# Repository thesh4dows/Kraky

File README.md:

# Kraky

Kraky is a DIY open-hardware project inspired by the Flipper Zero. It uses affordable parts and focuses on an educational, modular, and easy to repair aspect.

I started this journey with just a sketchbook and a lot of passion. The first thing i did was look up all the components and make a list, so i would have a clear path for the next steps.
Then i've done the elettric schematic, once i redacted all the components i started with the elettric schematic and connecting all the components to outline the scheme for the PCB.
Once i've connected all the components i've moved on making the PCB, making the PCB was easy because all the connections where there the only problem was not get tangled in that mess but i've succeded.
With all the elettronics sorted out i moved on with the CAD and firmware, and even if they are a bit rought i'm looking forward to improving them.

For the assemble I suggest putting first the TP4056 and the U.FL connector, because they are smd soldered, and then I suggest putting the RFM98W-433S2, because is the module with the smallest pins, and the you can decide freely the order of the soldering from now on, you can also decide to use some header pins so you can use the modules in other projects.

---

## Main Components

| Function | Component |
|--------|----------|
| Logic board / Wi-Fi / Bluetooth | **ESP32-S3** |
| Sub-GHz | **RFM98W-433S2** |
| RFID | **RDM6300** |
| NFC | **PN532** |
| Battery charger | **TP4056** |
| Battery | **1000 mAh Li-ion** |
| IR Receiver | **TSOP38238** |
| IR Transmitter | **IR LED** |
| Speaker | **Passive** |
| GPIO Expansion | **10 Female GPIO pins** |
| microSD Slot | **CM1624** *(not yet implemented in PCB)* |
| Buttons | **4 tactile buttons** |
| Oscilloscope | **MPU6050** |
| Display | **Oled Display** |

---

## Future Features 

- microSD support
- new pcb more small
- modularity

---

## WIRING DIAGRAM

---

## PCB 

---

## PCB AND 3D RENDER COMBINED

---

## BOM LIST
| Component | Link |
|--------|----------|
| **ESP32-S3** | [Aliexpress](https://it.aliexpress.com/item/1005009962649997.html?spm=a2g0o.cart.0.0.5d8818fcuRNXq9&mp=1&pdp_npi=6%40dis%21EUR%21EUR%208.05%21EUR%207.33%21%21EUR%207.33%21%21%21%4021038e1e17694574608762210ead3b%2112000050714164641%21ct%21IT%214906144315%21%211%210%21&gatewayAdapt=glo2ita) |
| **RFM98W-433S2** | [Aliexpress](https://it.aliexpress.com/item/1005008889705168.html?spm=a2g0o.cart.0.0.5d8818fcuRNXq9&mp=1&pdp_npi=6%40dis%21EUR%21EUR%2013.69%21EUR%2013.69%21%21EUR%2013.69%21%21%21%4021038e1e17694574632892284ead3b%2112000047093365845%21ct%21IT%214906144315%21%211%210%21&gatewayAdapt=glo2ita) |
| **RDM6300** | [Aliexpress](https://it.aliexpress.com/item/32878097013.html?spm=a2g0o.cart.0.0.5d8818fcuRNXq9&mp=1&pdp_npi=6%40dis%21EUR%21EUR%203.16%21EUR%203.16%21%21EUR%203.16%21%21%21%4021038e1e17694574632892284ead3b%2165586589948%21ct%21IT%214906144315%21%211%210%21&gatewayAdapt=glo2ita) |
| **PN532** | [Aliexpress](https://it.aliexpress.com/item/1005008554785133.html?spm=a2g0o.cart.0.0.5d8818fcuRNXq9&mp=1&pdp_npi=6%40dis%21EUR%21EUR%206.69%21EUR%203.07%21%21EUR%203.01%21%21%21%4021038e1e17694574608762210ead3b%2112000045690199375%21ct%21IT%214906144315%21%211%210%21&gatewayAdapt=glo2ita) |
| **TP4056** | [Aliexpress](https://it.aliexpress.com/item/1005006520142503.html?spm=a2g0o.productlist.main.9.370dQqVLQqVLdw&algo_pvid=b4bbd4a5-a930-4122-b394-fd39a9f770f2&algo_exp_id=b4bbd4a5-a930-4122-b394-fd39a9f770f2-8&pdp_ext_f=%7B%22order%22%3A%2220%22%2C%22spu_best_type%22%3A%22price%22%2C%22eval%22%3A%221%22%2C%22fromPage%22%3A%22search%22%7D&pdp_npi=6%40dis%21EUR%219.23%214.34%21%21%2174.32%2134.93%21%402103834817694577274995958e83e4%2112000037514108642%21sea%21IT%214906144315%21X%211%210%21n_tag%3A-29919%3Bd%3Af5869dfc%3Bm03_new_user%3A-29895&curPageLogUid=HOVHMltfnK6x&utparam-url=scene%3Asearch%7Cquery_from%3A%7Cx_object_id%3A1005006520142503%7C_p_origin_prod%3A) |
| **Battery** | [Aliexpress](https://it.aliexpress.com/item/1005006284232365.html?spm=a2g0o.cart.0.0.1eb718fcbElXUV&mp=1&pdp_npi=6%40dis%21EUR%21EUR%2017.40%21EUR%2010.09%21%21EUR%209.59%21%21%21%4021038e1e17694577674865712ead3b%2112000036605860873%21ct%21IT%214906144315%21%211%210%21&gatewayAdapt=glo2ita) |
| **TSOP38238** | [Aliexpress](https://it.aliexpress.com/item/32949322622.html?spm=a2g0o.cart.0.0.1eb718fcbElXUV&mp=1&pdp_npi=6%40dis%21EUR%21EUR%202.24%21EUR%202.24%21%21EUR%202.24%21%21%21%4021038e1e17694577674865712ead3b%2166318108356%21ct%21IT%214906144315%21%211%210%21&gatewayAdapt=glo2ita) |
| IR LED | [Aliexpress](https://it.aliexpress.com/item/1005006286672244.html?spm=a2g0o.detail.0.0.5c75OQANOQANd8&mp=1&pdp_npi=6%40dis%21EUR%21EUR%201.24%21EUR%201.24%21%21EUR%201.24%21%21%21%40211b431017709169710087494e4c02%2112000036615490369%21ct%21IT%214906144315%21%211%210%21&pdp_ext_f=%7B%22cart2PdpParams%22%3A%7B%22pdpBusinessMode%22%3A%22retail%22%7D%7D&_gl=1*5a8ami*_gcl_aw*R0NMLjE3NzAyMTg4NDcuQ2owS0NRaUEtWXZNQmhEdEFSSXNBSFp1VXpJOWRqODVuQVpGTGNfQ01JM29Qc2NQNFczWDk2NVR4YWJFX1FHRkNUZU5fZFY5YWdlb3RvMGFBamw1RUFMd193Y0I.*_gcl_dc*R0NMLjE3NzAyMTg4NDcuQ2owS0NRaUEtWXZNQmhEdEFSSXNBSFp1VXpJOWRqODVuQVpGTGNfQ01JM29Qc2NQNFczWDk2NVR4YWJFX1FHRkNUZU5fZFY5YWdlb3RvMGFBamw1RUFMd193Y0I.*_gcl_au*MTk0Mzg4NTc4MC4xNzYzNzM5NDY4*_ga*MTEzNzE4MTYwMTA1MjIyMS4xNzI2NTAwNTQ2NTA5*_ga_VED1YSGNC7*czE3NzA5MTU1ODUkbzI1JGcxJHQxNzcwOTE3MDExJGoxNCRsMCRoMA..&gatewayAdapt=glo2ita) |
| Speaker | [Aliexpress](https://it.aliexpress.com/item/1005008743722885.html?spm=a2g0o.cart.0.0.1eb718fcbElXUV&mp=1&pdp_npi=6%40dis%21EUR%21EUR%204.31%21EUR%202.07%21%21EUR%202.05%21%21%21%4021038e1e17694577658065675ead3b%2112000046486255672%21ct%21IT%214906144315%21%211%210%21&gatewayAdapt=glo2ita) |
| 10 Female GPIO pins | [Aliexpress](https://it.aliexpress.com/item/1005008966856219.html?spm=a2g0o.productlist.main.7.400c469fw7ynlD&algo_pvid=9f47b1bf-4ccb-44b8-978c-11ec9fc6ee57&algo_exp_id=9f47b1bf-4ccb-44b8-978c-11ec9fc6ee57-6&pdp_ext_f=%7B%22order%22%3A%22554%22%2C%22eval%22%3A%221%22%2C%22fromPage%22%3A%22search%22%7D&pdp_npi=6%40dis%21EUR%211.36%211.21%21%21%211.57%211.40%21%4021038e1e17694578315316029ead41%2112000047493524680%21sea%21IT%214906144315%21X%211%210%21n_tag%3A-29919%3Bd%3Af5869dfc%3Bm03_new_user%3A-29895%3BpisId%3A5000000198855826&curPageLogUid=SOrvoxlj0a91&utparam-url=scene%3Asearch%7Cquery_from%3A%7Cx_object_id%3A1005008966856219%7C_p_origin_prod%3A) |
| **10pF** | [Aliexpress](https://it.aliexpress.com/item/4001146250895.html?spm=a2g0o.productlist.main.12.6001XDEgXDEgfW&aem_p4p_detail=202602120809274082320741397240005427668&algo_pvid=a04d9bc2-151b-457c-b0a5-42ba286d77e0&algo_exp_id=a04d9bc2-151b-457c-b0a5-42ba286d77e0-11&pdp_ext_f=%7B%22order%22%3A%2288%22%2C%22eval%22%3A%221%22%2C%22fromPage%22%3A%22search%22%7D&pdp_npi=6%40dis%21EUR%211.52%211.47%21%21%211.76%211.70%21%402103963717709125677277103e20f4%2110000014890782446%21sea%21IT%214906144315%21X%211%210%21n_tag%3A-29919%3Bd%3Af5869dfc%3Bm03_new_user%3A-29895&curPageLogUid=z2f4APj81CW1&utparam-url=scene%3Asearch%7Cquery_from%3A%7Cx_object_id%3A4001146250895%7C_p_origin_prod%3A&search_p4p_id=202602120809274082320741397240005427668_3) |
| Buttons | [Aliexpress](https://it.aliexpress.com/item/1005003751942617.html?spm=a2g0o.productlist.main.6.7b66UgMCUgMC2v&algo_pvid=90b119e5-116b-44ca-8d19-1b1e01badc9a&algo_exp_id=90b119e5-116b-44ca-8d19-1b1e01badc9a-5&pdp_ext_f=%7B%22order%22%3A%22457%22%2C%22eval%22%3A%221%22%2C%22fromPage%22%3A%22search%22%7D&pdp_npi=6%40dis%21EUR%212.68%212.32%21%21%2121.57%2118.69%21%40211b618e17694579682652136e0d37%2112000027951043689%21sea%21IT%214906144315%21X%211%210%21n_tag%3A-29919%3Bd%3Af5869dfc%3Bm03_new_user%3A-29895%3BpisId%3A5000000198855826&curPageLogUid=h3YPZfgd06kE&utparam-url=scene%3Asearch%7Cquery_from%3A%7Cx_object_id%3A1005003751942617%7C_p_origin_prod%3A) |
| MPU6050 | [Aliexpress](https://it.aliexpress.com/item/1005010057794277.html?spm=a2g0o.cart.0.0.1eb718fcbElXUV&mp=1&pdp_npi=6%40dis%21EUR%21EUR%201.89%21EUR%201.89%21%21EUR%201.89%21%21%21%4021038e1e17694577658065675ead3b%2112000050979433010%21ct%21IT%214906144315%21%211%210%21&gatewayAdapt=glo2ita) |
| **100nF** | [Aliexpress](https://it.aliexpress.com/item/1005005691676032.html?spm=a2g0o.cart.0.0.1eb718fcbElXUV&mp=1&pdp_npi=6%40dis%21EUR%21EUR%202.24%21EUR%201.31%21%21EUR%201.31%21%21%21%4021038e1e17694577658065675ead3b%2112000034022594969%21ct%21IT%214906144315%21%211%210%21&gatewayAdapt=glo2ita) |
| **Battery connector** | [Aliexpress](https://it.aliexpress.com/item/1005009883885132.html?spm=a2g0o.cart.0.0.1eb718fcbElXUV&mp=1&pdp_npi=6%40dis%21EUR%21EUR%204.30%21EUR%201.92%21%21EUR%201.92%21%21%21%4021038e1e17694577658065675ead3b%2112000050645799497%21ct%21IT%214906144315%21%213%210%21&gatewayAdapt=glo2ita) |
| **2N3904** | [Aliexpress](https://it.aliexpress.com/item/1005009725419981.html?spm=a2g0o.cart.0.0.1eb718fcbElXUV&mp=1&pdp_npi=6%40dis%21EUR%21EUR%204.02%21EUR%201.89%21%21EUR%201.87%21%21%21%4021038e1e17694577658065675ead3b%2112000049959909602%21ct%21IT%214906144315%21%211%210%21&gatewayAdapt=glo2ita) |
| **BLM21PG331SN1D** | [Aliexpress](https://it.aliexpress.com/item/1005011660929872.html?spm=a2g0o.cart.0.0.447618fc6TVgoa&mp=1&pdp_npi=6%40dis%21EUR%21EUR%200.46%21EUR%200.45%21%21EUR%200.44%21%21%21%40211b431017709170583751647e4c02%2112000056178400547%21ct%21IT%214906144315%21%211%210%21&gatewayAdapt=glo2ita) | 
| **Antenna** | [Aliexpress](https://www.aliexpress.com/item/1005007502415094.html?spm=a2g0o.cart.0.0.235318fc7Us4Rx&mp=1&pdp_npi=6%40dis%21EUR%21EUR%201.47%21EUR%201.47%21%21EUR%201.47%21%21%21%40211b80f717697046718262403e31b3%2112000041044934823%21ct%21IT%214906144315%21%212%210%21) |
| **1K ohm** | [Aliexpress](https://it.aliexpress.com/item/1005008049421850.html?spm=a2g0o.productlist.main.5.339e2072xf4Fp6&algo_pvid=60a0f9d2-cb3a-4061-b250-3a89b5594825&algo_exp_id=60a0f9d2-cb3a-4061-b250-3a89b5594825-4&pdp_ext_f=%7B%22order%22%3A%221081%22%2C%22eval%22%3A%221%22%2C%22fromPage%22%3A%22search%22%7D&pdp_npi=6%40dis%21EUR%212.03%211.29%21%21%2116.36%2110.40%21%40211b61bb17694589696196228e2a30%2112000043433742591%21sea%21IT%214906144315%21X%211%210%21n_tag%3A-29919%3Bd%3Af5869dfc%3Bm03_new_user%3A-29895%3BpisId%3A5000000198855826&curPageLogUid=0AoDAOfCkDU4&utparam-url=scene%3Asearch%7Cquery_from%3A%7Cx_object_id%3A1005008049421850%7C_p_origin_prod%3A) |
| **10K ohm** | [Aliexpress](https://it.aliexpress.com/item/1005008049421850.html?spm=a2g0o.productlist.main.5.339e2072xf4Fp6&algo_pvid=60a0f9d2-cb3a-4061-b250-3a89b5594825&algo_exp_id=60a0f9d2-cb3a-4061-b250-3a89b5594825-4&pdp_ext_f=%7B%22order%22%3A%221081%22%2C%22eval%22%3A%221%22%2C%22fromPage%22%3A%22search%22%7D&pdp_npi=6%40dis%21EUR%212.03%211.29%21%21%2116.36%2110.40%21%40211b61bb17694589696196228e2a30%2112000043433742591%21sea%21IT%214906144315%21X%211%210%21n_tag%3A-29919%3Bd%3Af5869dfc%3Bm03_new_user%3A-29895%3BpisId%3A5000000198855826&curPageLogUid=0AoDAOfCkDU4&utparam-url=scene%3Asearch%7Cquery_from%3A%7Cx_object_id%3A1005008049421850%7C_p_origin_prod%3A) |
| **100 ohm** | [Aliexpress](https://it.aliexpress.com/item/1005008049421850.html?spm=a2g0o.productlist.main.5.339e2072xf4Fp6&algo_pvid=60a0f9d2-cb3a-4061-b250-3a89b5594825&algo_exp_id=60a0f9d2-cb3a-4061-b250-3a89b5594825-4&pdp_ext_f=%7B%22order%22%3A%221081%22%2C%22eval%22%3A%221%22%2C%22fromPage%22%3A%22search%22%7D&pdp_npi=6%40dis%21EUR%212.03%211.29%21%21%2116.36%2110.40%21%40211b61bb17694589696196228e2a30%2112000043433742591%21sea%21IT%214906144315%21X%211%210%21n_tag%3A-29919%3Bd%3Af5869dfc%3Bm03_new_user%3A-29895%3BpisId%3A5000000198855826&curPageLogUid=0AoDAOfCkDU4&utparam-url=scene%3Asearch%7Cquery_from%3A%7Cx_object_id%3A1005008049421850%7C_p_origin_prod%3A) |
| **Oled Display** | [Aliexpress](https://it.aliexpress.com/item/1005009180825215.html?spm=a2g0o.productlist.main.2.3d2d471bqR6akO&algo_pvid=3bf73457-57de-4609-b5e8-c52edf535fa0&algo_exp_id=3bf73457-57de-4609-b5e8-c52edf535fa0-1&pdp_ext_f=%7B%22order%22%3A%2279%22%2C%22eval%22%3A%221%22%2C%22fromPage%22%3A%22search%22%7D&pdp_npi=6%40dis%21EUR%213.36%213.06%21%21%213.90%213.55%21%402103890917695190995271643e41ef%2112000048217113638%21sea%21IT%214906144315%21X%211%210%21n_tag%3A-29919%3Bd%3Af5869dfc%3Bm03_new_user%3A-29895%3BpisId%3A5000000198855826&curPageLogUid=jkERcBiiep5C&utparam-url=scene%3Asearch%7Cquery_from%3A%7Cx_object_id%3A1005009180825215%7C_p_origin_prod%3A) |
| **Led** | [Aliexpress](https://it.aliexpress.com/item/1005006463058075.html?spm=a2g0o.productlist.main.5.705af8d9MykV40&algo_pvid=cd9d209a-c5d1-4345-918b-1aef88c26f78&algo_exp_id=cd9d209a-c5d1-4345-918b-1aef88c26f78-4&pdp_ext_f=%7B%22order%22%3A%221437%22%2C%22spu_best_type%22%3A%22price%22%2C%22eval%22%3A%221%22%2C%22fromPage%22%3A%22search%22%7D&pdp_npi=6%40dis%21EUR%211.66%211.17%21%21%2113.42%219.48%21%402103834817695464502855059e28c6%2112000037284712619%21sea%21IT%210%21ABX%211%210%21n_tag%3A-29910%3Bd%3Af5869dfc%3Bm03_new_user%3A-29895%3BpisId%3A5000000197840834&curPageLogUid=CU7YloDPjo8Z&utparam-url=scene%3Asearch%7Cquery_from%3A%7Cx_object_id%3A1005006463058075%7C_p_origin_prod%3A) |
| **Step Up** | [Aliexpress](https://it.aliexpress.com/item/1005010399811030.html?spm=a2g0o.detail.0.0.5c75OQANOQANd8&mp=1&pdp_npi=6%40dis%21EUR%21EUR%205.30%21EUR%202.54%21%21EUR%202.52%21%21%21%40211b431017709169710087494e4c02%2112000052282921768%21ct%21IT%214906144315%21%211%210%21&_gl=1*nbieyi*_gcl_aw*R0NMLjE3NzAyMTg4NDcuQ2owS0NRaUEtWXZNQmhEdEFSSXNBSFp1VXpJOWRqODVuQVpGTGNfQ01JM29Qc2NQNFczWDk2NVR4YWJFX1FHRkNUZU5fZFY5YWdlb3RvMGFBamw1RUFMd193Y0I.*_gcl_dc*R0NMLjE3NzAyMTg4NDcuQ2owS0NRaUEtWXZNQmhEdEFSSXNBSFp1VXpJOWRqODVuQVpGTGNfQ01JM29Qc2NQNFczWDk2NVR4YWJFX1FHRkNUZU5fZFY5YWdlb3RvMGFBamw1RUFMd193Y0I.*_gcl_au*MTk0Mzg4NTc4MC4xNzYzNzM5NDY4*_ga*MTEzNzE4MTYwMTA1MjIyMS4xNzI2NTAwNTQ2NTA5*_ga_VED1YSGNC7*czE3NzA5MTU1ODUkbzI1JGcxJHQxNzcwOTE2OTcwJGo1NSRsMCRoMA..&gatewayAdapt=glo2ita) |
| **Switch** | [Aliexpress](https://it.aliexpress.com/item/1005004402594340.html?spm=a2g0o.productlist.main.8.6821RzZiRzZivU&aem_p4p_detail=20260128050330766496466031320001147087&algo_pvid=5d157c24-975d-4016-b80c-94e148440976&algo_exp_id=5d157c24-975d-4016-b80c-94e148440976-7&pdp_ext_f=%7B%22order%22%3A%22724%22%2C%22spu_best_type%22%3A%22service%22%2C%22eval%22%3A%221%22%2C%22fromPage%22%3A%22search%22%7D&pdp_npi=6%40dis%21EUR%212.14%211.87%21%21%212.51%212.20%21%40211b813b17696054100286413e9a8e%2112000029051761216%21sea%21IT%214906144315%21X%211%210%21n_tag%3A-29919%3Bd%3Af5869dfc%3Bm03_new_user%3A-29895%3BpisId%3A5000000198855826&curPageLogUid=7JLAO8Dg6auy&utparam-url=scene%3Asearch%7Cquery_from%3A%7Cx_object_id%3A1005004402594340%7C_p_origin_prod%3A&search_p4p_id=20260128050330766496466031320001147087_2) |
| **U.FL connector** | [Aliexpress](https://www.aliexpress.com/item/4001125536245.html?spm=a2g0o.cart.0.0.235318fc7Us4Rx&mp=1&pdp_npi=6%40dis%21EUR%21EUR%201.94%21EUR%201.90%21%21EUR%201.90%21%21%21%40211b80f717697046718262403e31b3%2110000014628446564%21ct%21IT%214906144315%21%211%210%21) |

---

## Responsible Use

Kraky is built to make it easier for anyone to explore and understand how multifunction electronic devices work in everyday life.
It’s not intended for bypassing security systems or breaking any laws.

All features are implemented with an educational and experimental focus.

---

## Tools Used

- KiCad 9
- Fusion360
- PlatformIO

---

## Project Status

This project is **work in progress (WIP)**.  
Future updates will include:

- microSD implementation
- firmware development
- smaller PCB and SMD soldered components 

---

## Contributing

Kraky is an **open and educational project**.  
Feedback, suggestions, and improvements are always welcome.

---

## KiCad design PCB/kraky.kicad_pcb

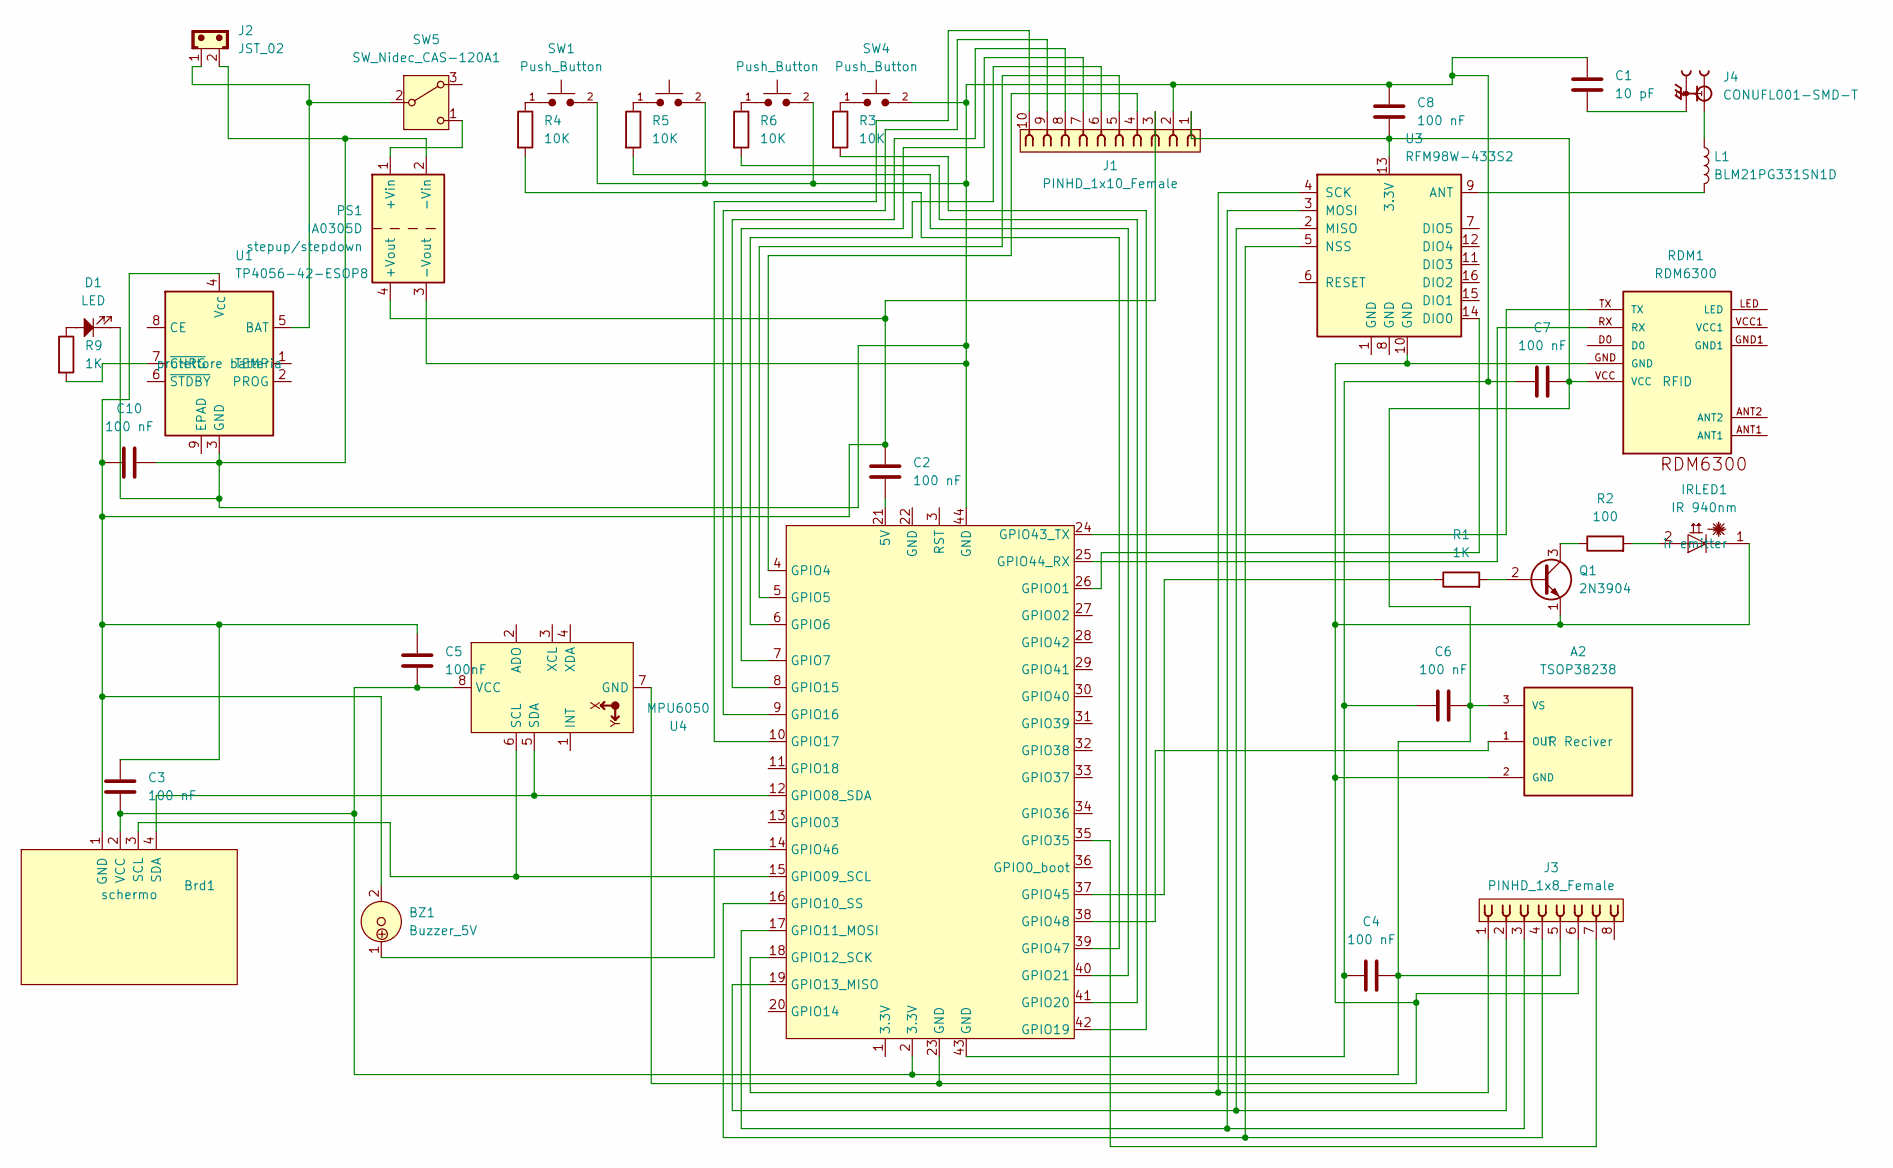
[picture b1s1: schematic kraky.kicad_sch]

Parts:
A2: TSOP38238; XDCR_TSOP38238; PARTREV 1.7
BZ1: Buzzer_5V; MagneticBuzzer_ProSignal_ABT-410-RC
Brd1: SSD1306; 128x64OLED
C1: 10 pF; C_Axial_L3.8mm_D2.6mm_P7.50mm_Horizontal
C2, C3, C4, C6, C7, C8, C10: 100 nF; C_Axial_L3.8mm_D2.6mm_P7.50mm_Horizontal
C5: 100nF; C_Axial_L3.8mm_D2.6mm_P7.50mm_Horizontal
D1: LED; LED_D5.0mm
IRLED1: IR 940nm; LED_D5.0mm
J1: PINHD_1x10_Female; PinSocket_1x10_P2.54mm_Vertical
J2: JST_02; JST_EH_B2B-EH-A_1x02_P2.50mm_Vertical
J3: PINHD_1x8_Female; PinSocket_1x08_P2.54mm_Vertical
J4: CONUFL001-SMD-T; LINX_CONUFL001-SMD-T
L1: BLM21PG331SN1D; R_0805_2012Metric
PS1: IA0305D; step up kraky
Q1: 2N3904; TO-92_Inline
R1, R9: 1K; R_Axial_DIN0204_L3.6mm_D1.6mm_P5.08mm_Horizontal
R2: 100; R_Axial_DIN0204_L3.6mm_D1.6mm_P5.08mm_Horizontal
R3, R4, R5, R6: 10K; R_Axial_DIN0204_L3.6mm_D1.6mm_P5.08mm_Horizontal
RDM1: RDM6300
SW1, SW2, SW3, SW4: Push_Button; SW_PUSH_6mm
SW5: SW_Nidec_CAS-120A1; SW_Slide_SPDT_Angled_CK_OS102011MA1Q
U1: TP4056-42-ESOP8; SOIC-8-1EP_3.9x4.9mm_P1.27mm_EP2.41x3.3mm_ThermalVias
U2: esp32-s3
U3: RFM98W-433S2; HOPERF_RFM9XW_THT
U4: MPU6050; MPU6050_Breakout

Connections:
unnamed: A2.2 (GND), IRLED1.1 (C), J3.6, Q1.1 (E), RDM1.GND, U2.23 (GND), U3.10 (GND), U4.7 (GND)
unnamed: A2.1 (OUT), U2.38 (GPIO48)
unnamed: A2.3 (VS), Brd1.2 (VCC), C3.2, C4.1, C5.2, C6.1, C7.1, C8.2, J1.1, J3.5, RDM1.VCC, U2.2 (3.3V), U3.13 (3.3V), U4.8 (VCC)
unnamed: BZ1.2, Brd1.1 (GND), C2.1, C3.1, C5.1, C10.1, J1.3, PS1.4 (+Vout), U1.4 (V_{CC})
unnamed: Brd1.3 (SCL), U2.15 (GPIO09_SCL), U4.6 (SCL)
unnamed: Brd1.4 (SDA), U2.12 (GPIO08_SDA), U4.5 (SDA)
unnamed: C1.2, J4.2, J4.3
unnamed: D1.2, R9.1
unnamed: IRLED1.2 (A), R2.2
unnamed: J4.1, L1.1
unnamed: PS1.1 (+Vin), SW5.1 (C)
unnamed: C1.1, C4.2, C6.2, C7.2, C8.1, C10.2, D1.1, J1.2, J2.2, PS1.2 (-Vin), PS1.3 (-Vout), SW1.2, SW2.2, SW3.2, SW4.2, U1.3 (GND), U2.43 (GND), U2.44 (GND)
unnamed: Q1.2 (B), R1.2
unnamed: Q1.3 (C), R2.1
unnamed: R3.1, SW4.1
unnamed: R4.1, SW1.1
unnamed: R5.1, SW2.1
unnamed: R6.1, SW3.1
unnamed: J2.1, SW5.2 (B), U1.5 (BAT)
unnamed: R9.2, U1.7 (~CHRG)
unnamed: C2.2, U2.21 (5V)
unnamed: U2.26 (GPIO01), U3.14 (DIO0)
unnamed: J1.4, U2.4 (GPIO4)
unnamed: J1.5, U2.5 (GPIO5)
unnamed: J1.6, U2.6 (GPIO6)
unnamed: J1.7, U2.7 (GPIO7)
unnamed: J3.4, U2.16 (GPIO10_SS), U3.5 (NSS)
unnamed: J3.3, U2.17 (GPIO11_MOSI), U3.3 (MOSI)
unnamed: J3.1, U2.18 (GPIO12_SCK), U3.4 (SCK)
unnamed: J3.2, U2.19 (GPIO13_MISO), U3.2 (MISO)
unnamed: J1.8, U2.8 (GPIO15)
unnamed: J1.9, U2.9 (GPIO16)
unnamed: J1.10, U2.10 (GPIO17)
unnamed: R3.2, U2.42 (GPIO19)
unnamed: R6.2, U2.41 (GPIO20)
unnamed: R5.2, U2.40 (GPIO21)
unnamed: J3.7, U2.35 (GPIO35)
unnamed: RDM1.TX, U2.24 (GPIO43_TX)
unnamed: RDM1.RX, U2.25 (GPIO44_RX)
unnamed: R1.1, U2.37 (GPIO45)
unnamed: BZ1.1, U2.14 (GPIO46)
unnamed: R4.2, U2.39 (GPIO47)
unnamed: L1.2, U3.9 (ANT)

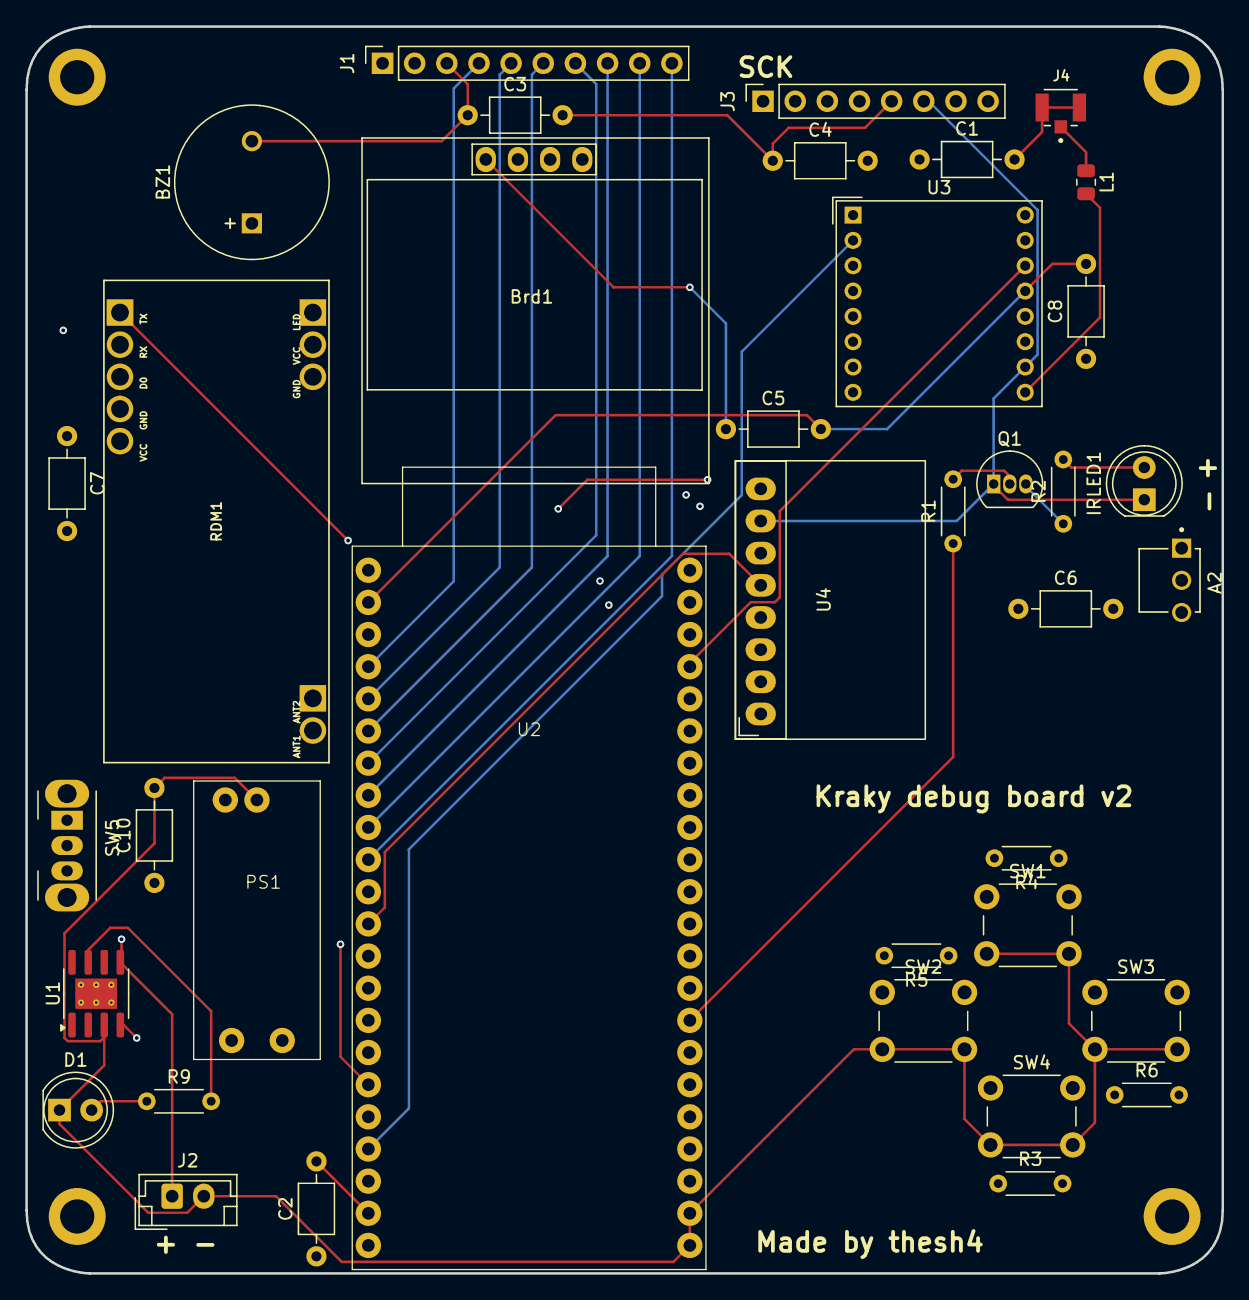
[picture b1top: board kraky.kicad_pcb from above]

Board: 4 copper layers, 94.5 x 98.5 mm, 42 parts (0 on the bottom side), 43 nets.

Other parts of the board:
buco1, buco2, buco3, buco4: MountingHole_2.7mm_M2.5_ISO14580_Pad

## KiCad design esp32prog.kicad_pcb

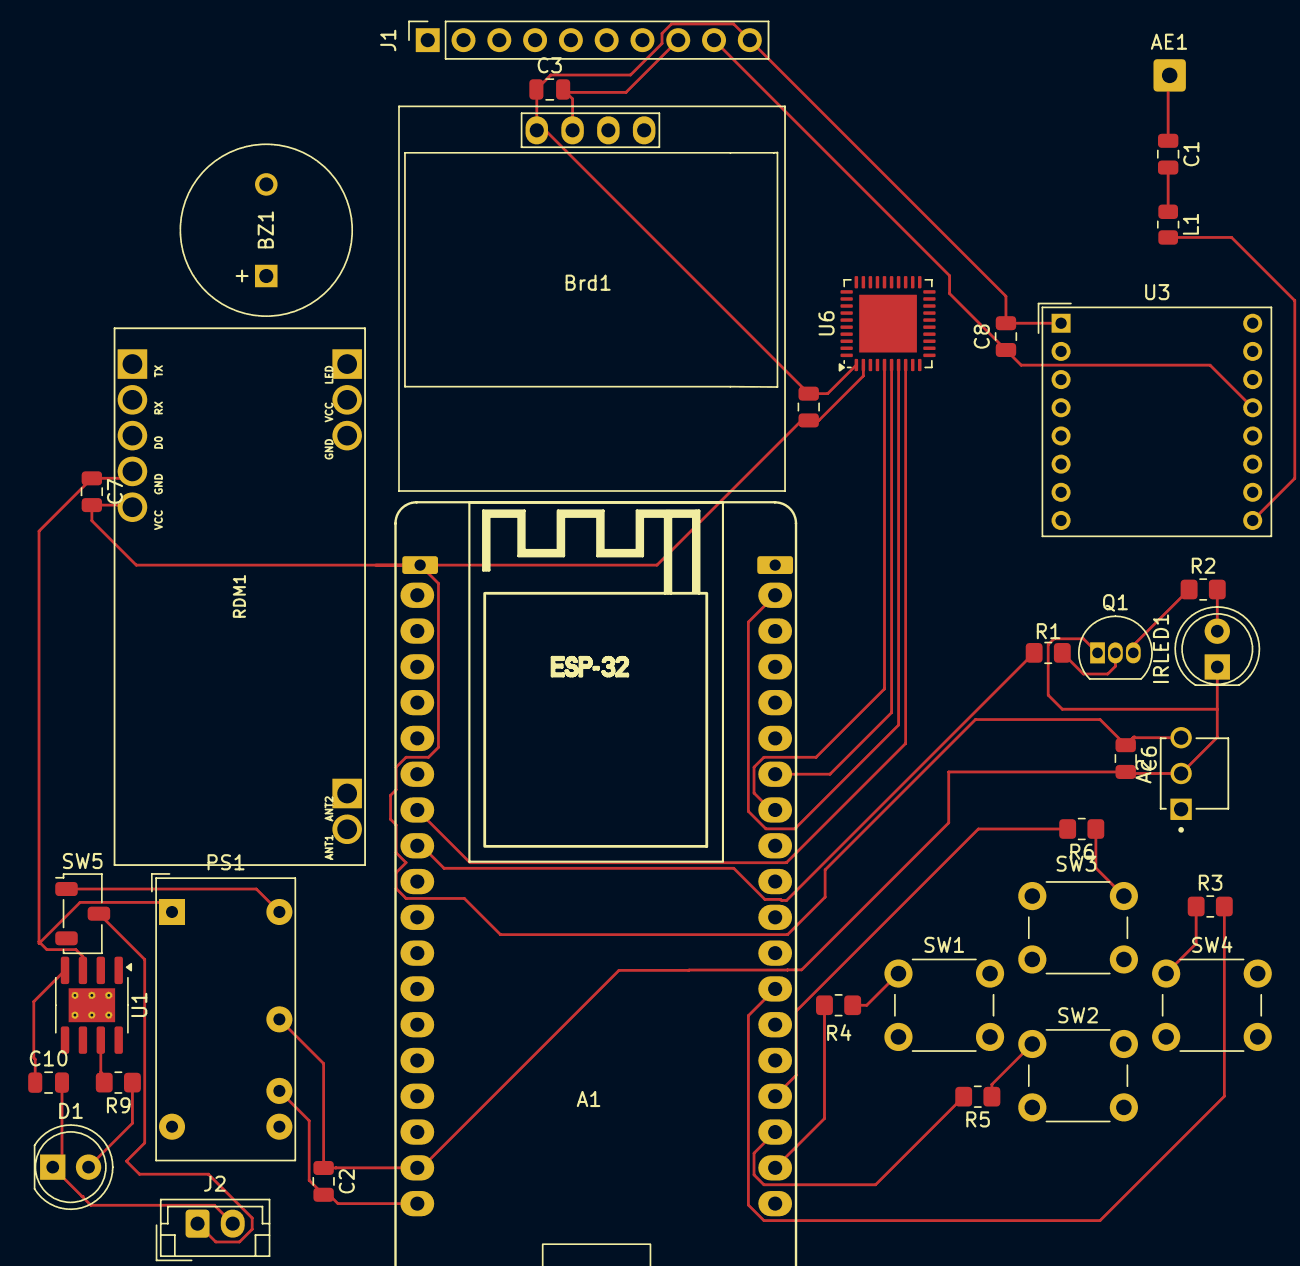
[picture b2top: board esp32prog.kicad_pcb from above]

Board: 4 copper layers, 36 parts (0 on the bottom side), 43 nets.

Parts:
A1: ESP32_DevKit_V1_DOIT_36GPIOs; DOIT_ESP32_DEVKIT_36Pins
A2: TSOP38238; XDCR_TSOP38238
AE1: Antenna; SolderWire-0.5sqmm_1x01_D0.9mm_OD2.3mm
BZ1: Buzzer_5V; MagneticBuzzer_ProSignal_ABT-410-RC
Brd1: SSD1306; 128x64OLED
C1: 10 pF; C_0805_2012Metric
C2, C3, C4, C6, C7, C8, C10: 100 nF; C_0805_2012Metric
D1: LED; LED_D5.0mm
IRLED1: IR 940nm; LED_D5.0mm
J1: PINHD_1x10_Female; PinSocket_1x10_P2.54mm_Vertical
J2: JST_02; JST_EH_B2B-EH-A_1x02_P2.50mm_Vertical
L1: BLM21PG331SN1D; R_0805_2012Metric
PS1: IA0305D; Converter_DCDC_XP_POWER-IAxxxxD_THT
Q1: 2N3904; TO-92_Inline
R1, R9: 1K; R_0805_2012Metric_Pad1.20x1.40mm_HandSolder
R2: 100; R_0805_2012Metric_Pad1.20x1.40mm_HandSolder
R3, R4, R5, R6: 10K; R_0805_2012Metric_Pad1.20x1.40mm_HandSolder
RDM1: RDM6300
SW1, SW2, SW3, SW4: Push_Button; SW_PUSH_6mm
SW5: SW_Nidec_CAS-120A1; Nidec_Copal_CAS-120A
U1: TP4056-42-ESOP8; SOIC-8-1EP_3.9x4.9mm_P1.27mm_EP2.41x3.3mm_ThermalVias
U3: RFM98W-433S2; HOPERF_RFM9XW_THT
U6: PN532; HVQFN-40-1EP_6x6mm_P0.5mm_EP4.1x4.1mm

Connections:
unnamed: A1.37 (5V), Brd1.2 (VCC), C3.2, C10.1, J1.8, U1.4 (V_{CC})
unnamed: A1.24 (ADC1_CH4/D32), U6.11 (IRQ)
unnamed: A1.25 (ADC1_CH5/D33), U6.8 (SS)
unnamed: A1.22 (ADC1_CH6/D34), J1.4
unnamed: A1.23 (ADC1_CH7/D35), J1.7
unnamed: A1.31 (ADC2_CH4/D13), J1.1
unnamed: A1.29 (ADC2_CH6/D14), J1.2
unnamed: A1.28 (ADC2_CH7/D27), J1.3
unnamed: A1.2 (CLK/GPIO6), R4.2
unnamed: A1.7 (D2), R3.2
unnamed: A1.8 (D4), U3.14 (DIO0)
unnamed: A1.11 (D5), U3.5 (NSS)
unnamed: A1.12 (D18), U3.4 (SCK), U6.5 (SCK)
unnamed: A1.13 (D19), U3.2 (MISO), U6.6 (MISO)
unnamed: A1.14 (D21/SDA), Brd1.4 (SDA)
unnamed: A1.17 (D22/SCL), Brd1.3 (SCL)
unnamed: A1.18 (D23), U3.3 (MOSI), U6.7 (MOSI)
unnamed: A1.26 (DAC1/ADC2_CH8/D25), R1.1
unnamed: A1.27 (DAC2/ADC2_CH9/D26), A2.1 (OUT)
unnamed: A1.35 (GND), A2.2 (GND), BZ1.2, Brd1.1 (GND), C2.1, C3.1, C4.2, C6.2, C7.1, C8.2, C10.2, D1.1, IRLED1.1 (C), J1.10, J2.2, PS1.1 (-Vin), PS1.4 (-Vout), Q1.1 (E), RDM1.GND, SW1.2, SW2.2, SW3.2, SW4.2, U1.3 (GND), U3.1 (GND), U6.1 (GND)
unnamed: A1.33 (GPIO10/SD3), RDM1.RX
unnamed: A1.34 (GPIO11/CMD), RDM1.TX
unnamed: A1.20 (GPIO36/ADC1_CH0/VP), J1.6
unnamed: A1.21 (GPIO39/ADC1_CH3/VN), J1.5
unnamed: A1.15 (RX0/GPIO3), BZ1.1
unnamed: A1.3 (SD0/GPIO7), R5.2
unnamed: A1.4 (SD1/GPIO8), R6.2
unnamed: A1.36 (VIN), C2.2, PS1.5 (+Vout)
unnamed: A1.38 (3.3V), A2.3 (VS), C4.1, C6.1, C7.2, C8.1, J1.9, RDM1.VCC, U3.13 (3.3V), U6.2 (VCC)
unnamed: AE1.1 (A), C1.1
unnamed: C1.2, L1.1
unnamed: D1.2, R9.1
unnamed: IRLED1.2 (A), R2.2
unnamed: PS1.3 (+Vin), SW5.1 (C)
unnamed: Q1.2 (B), R1.2
unnamed: Q1.3 (C), R2.1
unnamed: R3.1, SW4.1
unnamed: R4.1, SW1.1
unnamed: R5.1, SW2.1
unnamed: R6.1, SW3.1
unnamed: J2.1, SW5.2 (B), U1.5 (BAT)
unnamed: R9.2, U1.7 (~CHRG)
unnamed: L1.2, U3.9 (ANT)

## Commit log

2025-12-05 initial scheme of the projecct
2025-12-18 first version of the electrical diagram
2025-12-31 third version of the elettric scheme
2026-01-03 3D render of the Kraky's enclosure
2026-01-04 this is the first version of the pcb
2026-01-04 this is the third version of the schematich
2026-01-04 this is a first and very simple version of the firmware
2026-01-05 this is the first version of the pcb, it's a debug board
2026-01-08 Rename esp32prog.kicad_pro to kraky.kicad_pro
2026-01-08 Rename esp32prog.csv to kraky.csv
2026-01-08 kraky's gerbers for pcb ordering
2026-01-11 new schematic with change in the esp32
2026-01-17 updated, read readme
2026-01-22 added female pins where i would put the PN532 because i couldn't find the library
2026-01-31 Create LICENSE
2026-01-31 Update issue templates
2026-02-12 Rename 3D render_.3mf to 3D renders / 3D render_.3mf
2026-02-12 PCB files
2026-02-12 Rename kraky.kicad_pro to PCB /kraky.kicad_pro
2026-02-12 3D renders
